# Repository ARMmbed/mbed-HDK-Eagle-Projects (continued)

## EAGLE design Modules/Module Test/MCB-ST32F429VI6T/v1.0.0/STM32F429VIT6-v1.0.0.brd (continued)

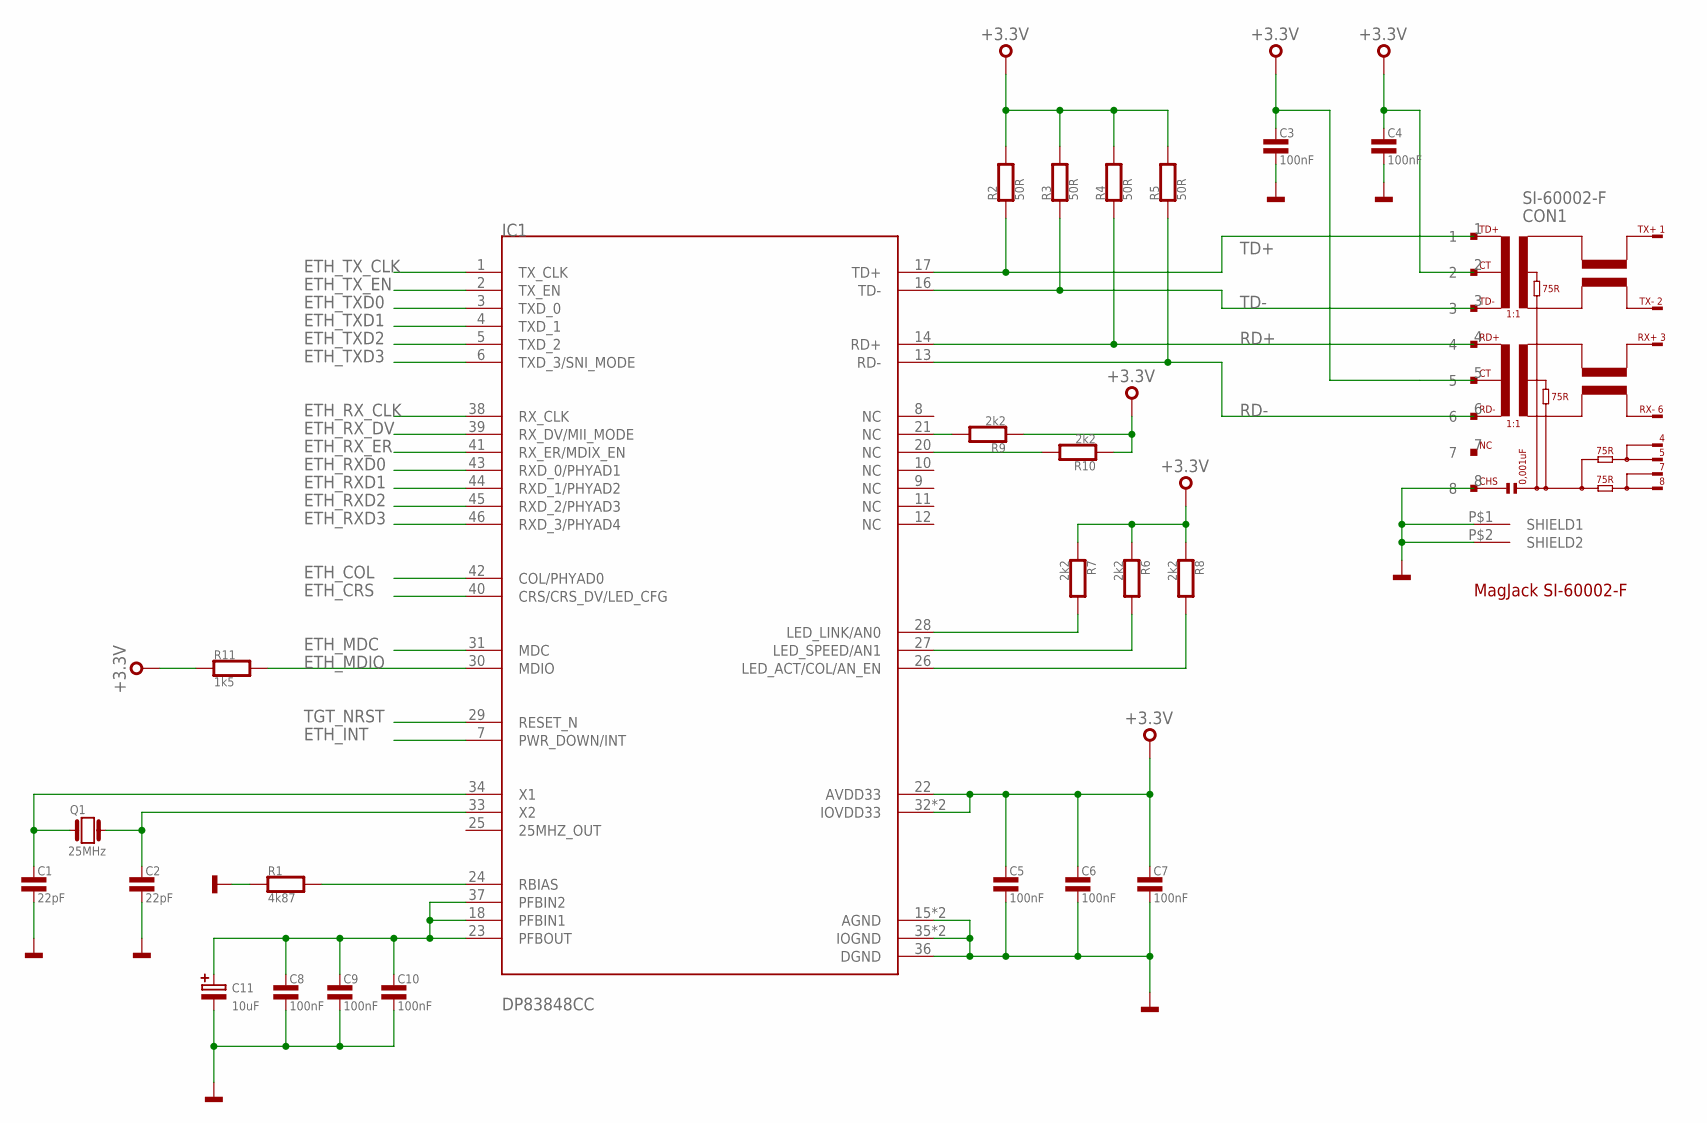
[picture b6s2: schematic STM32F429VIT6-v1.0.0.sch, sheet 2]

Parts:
C1, C2: 22pF; 0402
C3, C4, C5, C6, C7, C8, C9, C10: 100nF; 0402
C11: 10uF; SMC_A
CON1: SI-60002-F; RJ45
IC1: DP83848CC; LQFP-48
Q1: 25MHz; 3.2X.2.5
R1: 4k87; 0402
R2, R3, R4, R5: 50R; 0402
R6, R7, R8, R9, R10: 2k2; 0402
R11: 1k5; 0402

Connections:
+3.3V: C3.1, C4.1, C5.1, C6.1, C7.1, CON1.2, CON1.5, IC1.22 (AVDD33), IC1.32 (IOVDD33), IC1.48 (IOVDD33), R2.2, R3.2, R4.2, R5.2, R6.1, R7.1, R8.1, R9.1, R10.1, R11.1; also elsewhere on the board
ETH_COL: IC1.42 (COL/PHYAD0); also elsewhere on the board
ETH_CRS: IC1.40 (CRS/CRS_DV/LED_CFG); also elsewhere on the board
ETH_INT: IC1.7 (PWR_DOWN/INT); also elsewhere on the board
ETH_MDC: IC1.31 (MDC); also elsewhere on the board
ETH_MDIO: IC1.30 (MDIO), R11.2; also elsewhere on the board
ETH_RXD0: IC1.43 (RXD_0/PHYAD1); also elsewhere on the board
ETH_RXD1: IC1.44 (RXD_1/PHYAD2); also elsewhere on the board
ETH_RXD2: IC1.45 (RXD_2/PHYAD3); also elsewhere on the board
ETH_RXD3: IC1.46 (RXD_3/PHYAD4); also elsewhere on the board
ETH_RX_CLK: IC1.38 (RX_CLK); also elsewhere on the board
ETH_RX_DV: IC1.39 (RX_DV/MII_MODE); also elsewhere on the board
ETH_RX_ER: IC1.41 (RX_ER/MDIX_EN); also elsewhere on the board
ETH_TXD0: IC1.3 (TXD_0); also elsewhere on the board
ETH_TXD1: IC1.4 (TXD_1); also elsewhere on the board
ETH_TXD2: IC1.5 (TXD_2); also elsewhere on the board
ETH_TXD3: IC1.6 (TXD_3/SNI_MODE); also elsewhere on the board
ETH_TX_CLK: IC1.1 (TX_CLK); also elsewhere on the board
ETH_TX_EN: IC1.2 (TX_EN); also elsewhere on the board
GND: C1.2, C2.2, C3.2, C4.2, C5.2, C6.2, C7.2, C8.2, C9.2, C10.2, C11.-, CON1.8, CON1.P$1 (SHIELD1), CON1.P$2 (SHIELD2), IC1.15 (AGND), IC1.19 (AGND), IC1.35 (IOGND), IC1.36 (DGND), IC1.47 (IOGND), R1.1; also elsewhere on the board
unnamed: C1.1, IC1.34 (X1), Q1.P$1 (1)
unnamed: C2.1, IC1.33 (X2), Q1.P$3 (2)
unnamed: IC1.28 (LED_LINK/AN0), R7.2
unnamed: IC1.24 (RBIAS), R1.2
unnamed: IC1.27 (LED_SPEED/AN1), R6.2
unnamed: IC1.26 (LED_ACT/COL/AN_EN), R8.2
unnamed: IC1.21 (NC), R9.2
unnamed: IC1.20 (NC), R10.2
unnamed: C8.1, C9.1, C10.1, C11.+, IC1.18 (PFBIN1), IC1.23 (PFBOUT), IC1.37 (PFBIN2)
RD+: CON1.4, IC1.14 (RD+), R4.1
RD-: CON1.6, IC1.13 (RD-), R5.1
TD+: CON1.1, IC1.17 (TD+), R2.1
TD-: CON1.3, IC1.16 (TD-), R3.1
TGT_NRST: IC1.29 (RESET_N); also elsewhere on the board

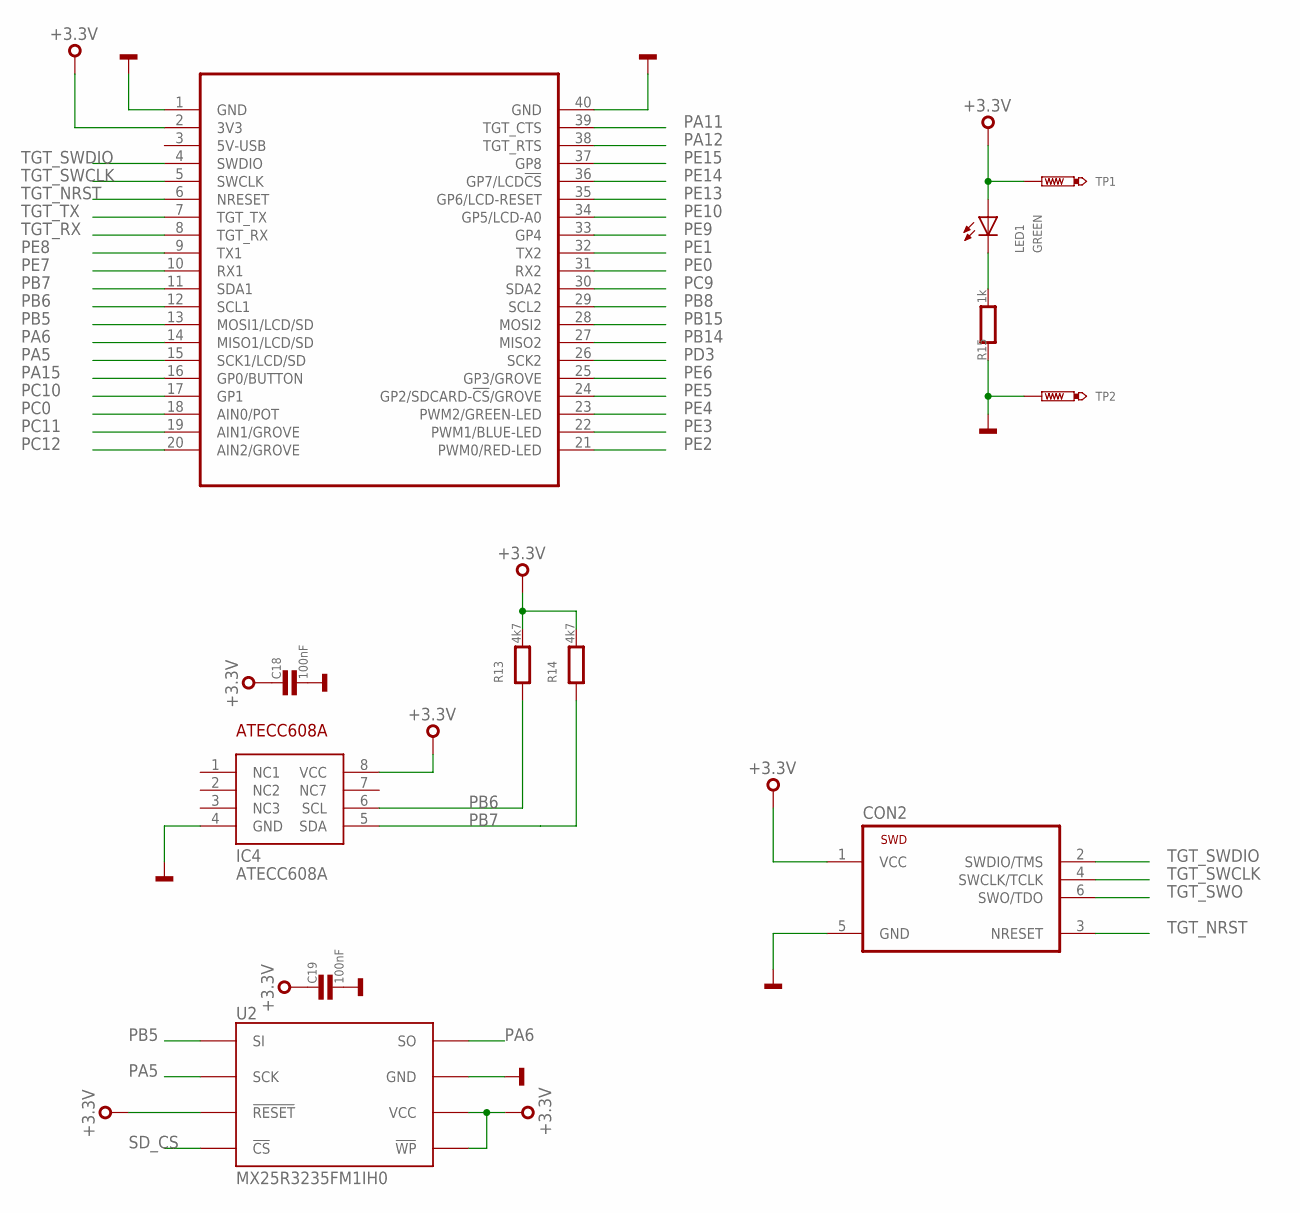
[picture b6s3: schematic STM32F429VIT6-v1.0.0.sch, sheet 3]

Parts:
C18, C19: 100nF; 0402
CON2: TC2030-CTX-NL
IC4: ATECC608A; SO8
LED1: GREEN; CHIPLED_0603
MOD1: MODULE_DAUGHTER
R13, R14: 4k7; 0402
R15: 1k; 0603
TP1, TP2: TEST-POINT-50R-PTH; TP50-PTH
U2: MX25R3235FM1IH0; SO8

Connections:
+3.3V: C18.1, C19.1, CON2.1 (VCC), IC4.8 (VCC), LED1.A, MOD1.2 (3V3), R13.2, R14.2, TP1.TP, U2.3 (!WP), U2.7 (!RESET), U2.8 (VCC); also elsewhere on the board
GND: C18.2, C19.2, CON2.5 (GND), IC4.4 (GND), MOD1.1 (GND), MOD1.40 (GND), R15.1, TP2.TP, U2.4 (GND); also elsewhere on the board
PA5: MOD1.15 (SCK1/LCD/SD), U2.6 (SCK); also elsewhere on the board
PA6: MOD1.14 (MISO1/LCD/SD), U2.2 (SO); also elsewhere on the board
PA11: MOD1.39 (TGT_CTS); also elsewhere on the board
PA12: MOD1.38 (TGT_RTS); also elsewhere on the board
PA15: MOD1.16 (GP0/BUTTON); also elsewhere on the board
PA_1: LED1.C, R15.2
PB5: MOD1.13 (MOSI1/LCD/SD), U2.5 (SI); also elsewhere on the board
PB6: IC4.6 (SCL), MOD1.12 (SCL1), R13.1; also elsewhere on the board
PB7: IC4.5 (SDA), MOD1.11 (SDA1), R14.1; also elsewhere on the board
PB8: MOD1.29 (SCL2); also elsewhere on the board
PB14: MOD1.27 (MISO2); also elsewhere on the board
PB15: MOD1.28 (MOSI2); also elsewhere on the board
PC0: MOD1.18 (AIN0/POT); also elsewhere on the board
PC9: MOD1.30 (SDA2); also elsewhere on the board
PC10: MOD1.17 (GP1); also elsewhere on the board
PC11: MOD1.19 (AIN1/GROVE); also elsewhere on the board
PC12: MOD1.20 (AIN2/GROVE); also elsewhere on the board
PD3: MOD1.26 (SCK2); also elsewhere on the board
PE0: MOD1.31 (RX2); also elsewhere on the board
PE1: MOD1.32 (TX2); also elsewhere on the board
PE2: MOD1.21 (PWM0/RED-LED); also elsewhere on the board
PE3: MOD1.22 (PWM1/BLUE-LED); also elsewhere on the board
PE4: MOD1.23 (PWM2/GREEN-LED); also elsewhere on the board
PE5: MOD1.24 (GP2/SDCARD-!CS!/GROVE); also elsewhere on the board
PE6: MOD1.25 (GP3/GROVE); also elsewhere on the board
PE7: MOD1.10 (RX1); also elsewhere on the board
PE8: MOD1.9 (TX1); also elsewhere on the board
PE9: MOD1.33 (GP4); also elsewhere on the board
PE10: MOD1.34 (GP5/LCD-A0); also elsewhere on the board
PE13: MOD1.35 (GP6/LCD-RESET); also elsewhere on the board
PE14: MOD1.36 (GP7/LCD!CS); also elsewhere on the board
PE15: MOD1.37 (GP8); also elsewhere on the board
SD_CS: U2.1 (!CS); also elsewhere on the board
TGT_NRST: CON2.3 (NRESET), MOD1.6 (NRESET); also elsewhere on the board
TGT_RX: MOD1.8 (TGT_RX); also elsewhere on the board
TGT_SWCLK: CON2.4 (SWCLK/TCLK), MOD1.5 (SWCLK); also elsewhere on the board
TGT_SWDIO: CON2.2 (SWDIO/TMS), MOD1.4 (SWDIO); also elsewhere on the board
TGT_SWO: CON2.6 (SWO/TDO); also elsewhere on the board
TGT_TX: MOD1.7 (TGT_TX); also elsewhere on the board

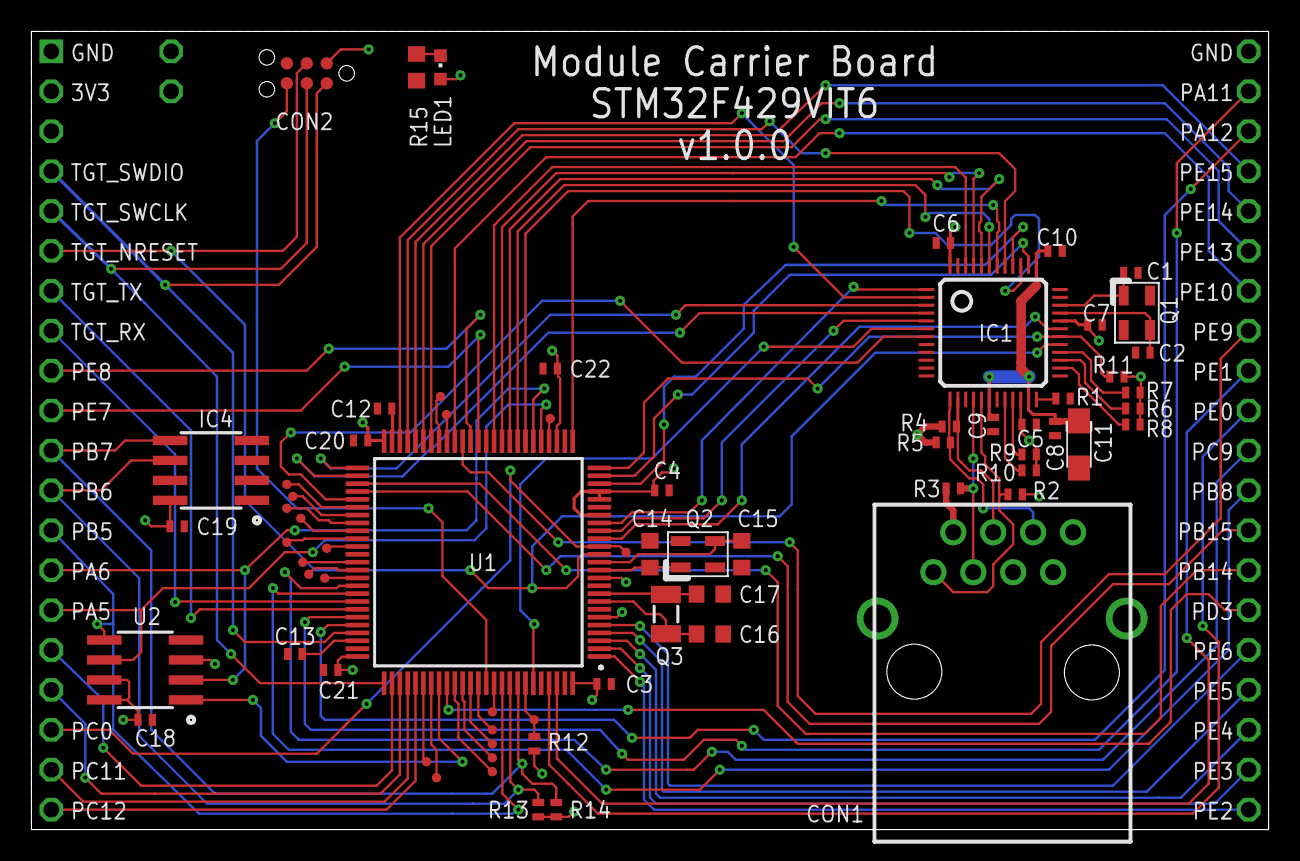
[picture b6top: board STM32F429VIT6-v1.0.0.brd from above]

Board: 2 copper layers, 78.7 x 50.8 mm, 71 parts (0 on the bottom side), 98 nets.

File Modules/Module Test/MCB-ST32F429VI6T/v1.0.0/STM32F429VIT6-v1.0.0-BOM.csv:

"Qty";"Value";"Device";"Package";"Parts";"Description";"MF";"MFN";"OC-DIGIKEY";"OC-MOUSER";"OC-NEWARK";"TP_SIGNAL_NAME";
"11";"100nF";"C0402";"0402";"C3, C4, C5, C6, C7, C8, C9, C10, C20, C21, C22";"Capacitor";"";"";"";"";"";"";
"2";"100nF";"CAPACITOR0402";"0402";"C18, C19";"Capacitor";"";"";"";"";"";"";
"1";"10k";"R0402";"0402";"R12";"Resistor";"";"";"";"";"";"";
"1";"10uF";"C-POLA";"SMC_A";"C11";"Polarised capacitor";"";"";"";"";"";"";
"1";"1k";"RESISTOR0603";"0603";"R15";"Resistor";"";"";"";"";"";"";
"1";"1k5";"R0402";"0402";"R11";"Resistor";"";"";"";"";"";"";
"2";"2.2uF";"C0402";"0402";"C12, C13";"Capacitor";"";"";"";"";"";"";
"2";"22pF";"C0402";"0402";"C1, C2";"Capacitor";"";"";"";"";"";"";
"4";"22pF";"C0603";"0603";"C14, C15, C16, C17";"Capacitor";"";"";"";"";"";"";
"2";"25MHz";"GENERIC-CRYSTAL_3.2X2.5";"3.2X.2.5";"Q1, Q2";"GENERIC Crystal";"";"";"";"";"";"";
"5";"2k2";"R0402";"0402";"R6, R7, R8, R9, R10";"Resistor";"";"";"";"";"";"";
"1";"32.768kHz";"GENERIC-CRYSTAL_FC135";"FC135";"Q3";"GENERIC Crystal";"";"";"";"";"";"";
"2";"4k7";"RESISTOR0402";"0402";"R13, R14";"Resistor";"";"";"";"";"";"";
"1";"4k87";"R0402";"0402";"R1";"Resistor";"";"";"";"";"";"";
"4";"50R";"R0402";"0402";"R2, R3, R4, R5";"Resistor";"";"";"";"";"";"";
"1";"ATECC608A";"ATECC608A";"SO8";"IC4";"";"";"";"";"";"";"";
"1";"DP83848CC";"DP83848CC";"LQFP-48";"IC1";"";"";"";"";"";"";"";
"1";"GREEN";"SMD_LED0603";"CHIPLED_0603";"LED1";"LED SMD, Colour Red";"Wurth Electronics Inc";"150060RS75000";"732-4978-1-ND";"710-150060RS75000";"2322071";"";
"1";"MODULE_DAUGHTER";"MODULE_DAUGHTER";"MODULE_DAUGHTER";"MOD1";"";"";"";"";"";"";"";
"1";"MX25R3235FM1IH0";"MX25R3235FM1IH0";"SO8";"U2";"Serial Flash 32 Mb 80 Mhz";"Macronix";"MX25R3235FM1IH0";"1092-1175-ND";"";"";"";
"21";"PTR1TP06R";"PTR1TP06R";"TP06R";"TP3, TP4, TP5, TP6, TP7, TP8, TP9, TP10, TP11, TP12, TP13, TP15, TP16, TP17, TP18, TP19, TP20, TP21, TP22, TP23, TP24";"TEST PIN";"";"";"";"";"";"";
"1";"SI-60002-F";"SI-60002-F";"RJ45";"CON1";"RJ45 Right Angle";"Stewart Connector";"SI-60002-F";"380-1105-ND";"";"24M7449";"";
"1";"STM32F429VIT6";"STM32F429VIT6";"QFP50P1600X1600X160-100N";"U1";"";"";"";"";"";"";"";
"1";"TC2030-CTX-NL";"TC2030-CTX-NL";"TC2030-CTX-NL";"CON2";"Tag-Connect In Circuit Programming & Debug Cable 6 Pin";"";"";"";"";"";"";
"2";"TEST-POINT-50R-PTH";"TEST-POINT-50R-PTH";"TP50-PTH";"TP1, TP2";"";"";"";"";"";"";"";
